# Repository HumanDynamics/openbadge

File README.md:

# OpenBadge project #

Welcome to the Open Badge project, an open-source framework and toolkit for measuring and shaping face-to-face social interactions using either custom hardware devices or smart phones, and real-time web-based visualizations. Open Badges is a modular system that allows researchers to monitor and collect interaction data from people engaged in real-life social settings. For more information, please read our main publications ([1](https://ieeexplore.ieee.org/document/8259434),[2](https://www.media.mit.edu/publications/rhythm-a-unified-measurement-platform-for-human-organizations/),[3](https://www.media.mit.edu/publications/open-badges-a-low-cost-toolkit-for-measuring-team-communication-and-dynamics/)) ,visit our [wiki](https://github.com/HumanDynamics/OpenBadge/wiki), or join our [discussion forum](https://groups.google.com/d/forum/rhythm-badges).

Additional repositories that are part of this project:
* https://github.com/mitmedialab/rhythm-badge-programmer - schematics, vector files and instructions for making a programming rig 

* https://github.com/HumanDynamics/openbadge-hub-py - a python based hub (base station) for pulling data from badges

* https://github.com/HumanDynamics/openbadge-hub - a Javascript/Cordova app that communicates with the badges and stores
 the data to a server
* https://github.com/HumanDynamics/openbadge-server - the backend server for the app

* https://github.com/HumanDynamics/openbadge-analysis - Python (2.7) package for loading and pre-processing badge data

* https://github.com/HumanDynamics/openbadge-analysis-examples - Examples showing how to use the analysis package

## Docker wrapper ##
The nRF working environment is now available as a Docker container. The following commands have been tested under Ubuntu
linux, but should work under iOS as well (with some modifications, especially to the device names).

Important notes:
1. The badge must be connected to the programmer before starting the docker (using docker-compose run)
2. Docker will mount the project directory under /app inside the container, so the container can see the latest changes
 (no need to build the container after every code change)

Commands:
* docker-compose build : builds the docker container "nrf". You must run this command at least once before calling
 docker-compose run.
* docker-compose run nrf <COMMAND> : where <COMMAND> is a command to run inside the container.
  * When calling make (e.g. make badge_03v6_noDebug flashUnlock flashErase  flashS130 flashAPP), the script will automatically
  change the working directory to the data_collector directory. You can see the different make options by calling:
  "docker-compose run nrf make"
* docker-compose run nrf bash : opens an interactive bash shell
* ./programming_loop_docker.sh [test/prod] : a utility used for programming a batch of badges. It will compile once, and
 then enters a loop. Each time a new badge is placed, it will be automatically programmed and its MAC address will be
 written to the macs.log file. For most purposes, use the "prod" command variables. The "test" option turns on serial
 output and other testing features and is not recommended for production.

If you are using a raspberry pi to run this code, please use the raspberry pi compose file (-f docker-compose-raspi.yml). For example `docker-compose -f docker-compose-raspi.yml build`.

## Firmware testing tools ##
The framework includes two tools for testing firmware code
* Badge terminal. The utility opens a connections to a badge and allows you to run simple commands. To run, use the following docker command: `docker-compose run nrf terminal <MAC ADDRESS>`
* Integration tests. These are tests designed for testing basic badge functionality. To run the tests, use the following docker command: `docker-compose run nrf run_all_tests <MAC ADDRESS>`

Note that in order to run the integration tests, you'll need to have a badge connected with a serial interface. A regular J-Link debugger/programmer does not include these. We recommend using a nRF51 dev-kit as a programmer for this purpose (see our wiki/documentations on how to make one).

## Badge testing procedure ##
The badge firmware includes a tester mode that can be used for testing new badges. 
To compile, use the badge_03v6_tester flag (or badge_03v4_tester, for older hardware). For example:
```
make badge_03v6_noDebug flashUnlock flashErase  flashS130 flashAPP
```

Or, when using docker:
```
docker-compose run nrf make badge_03v6_noDebug flashUnlock flashErase  flashS130 flashAPP
```

Once programmed, the badge uses the LEDs to indicate the status of the test:
1. Blink red LED several times, one for each test (EEPROM, Flash, etc)
2. Microphone test. When it starts, both green and red LEDs will turn on 
It then looks for quiet->noise->quiet->noise pattern, each section must be at least 200 ms long. 
This must be completed within 10 seconds.
In a quiet place, simply say "ahhhh" twice, with pause in between. Every time the noise passed the threshold, the LEDs 
will turn off
3. Accelerometer test. When it starts, both green and red LEDs will turn on. Simply shake the badge
4. Once done, the green LED will turn off for several seconds and then turn off

Example for known issues with badge manufacturing:
* LEDs not turning on - might be a problem with the LEDs themselves
* When microphone test starts, both LEDs will momentarily turn on and then off
This might indicate a problem in the microphone filter or amplifier circuit (the microphone saturates and noise level says high)

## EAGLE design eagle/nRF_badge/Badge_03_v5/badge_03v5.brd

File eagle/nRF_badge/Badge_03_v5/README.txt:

Note - we have not manufactured this version yet

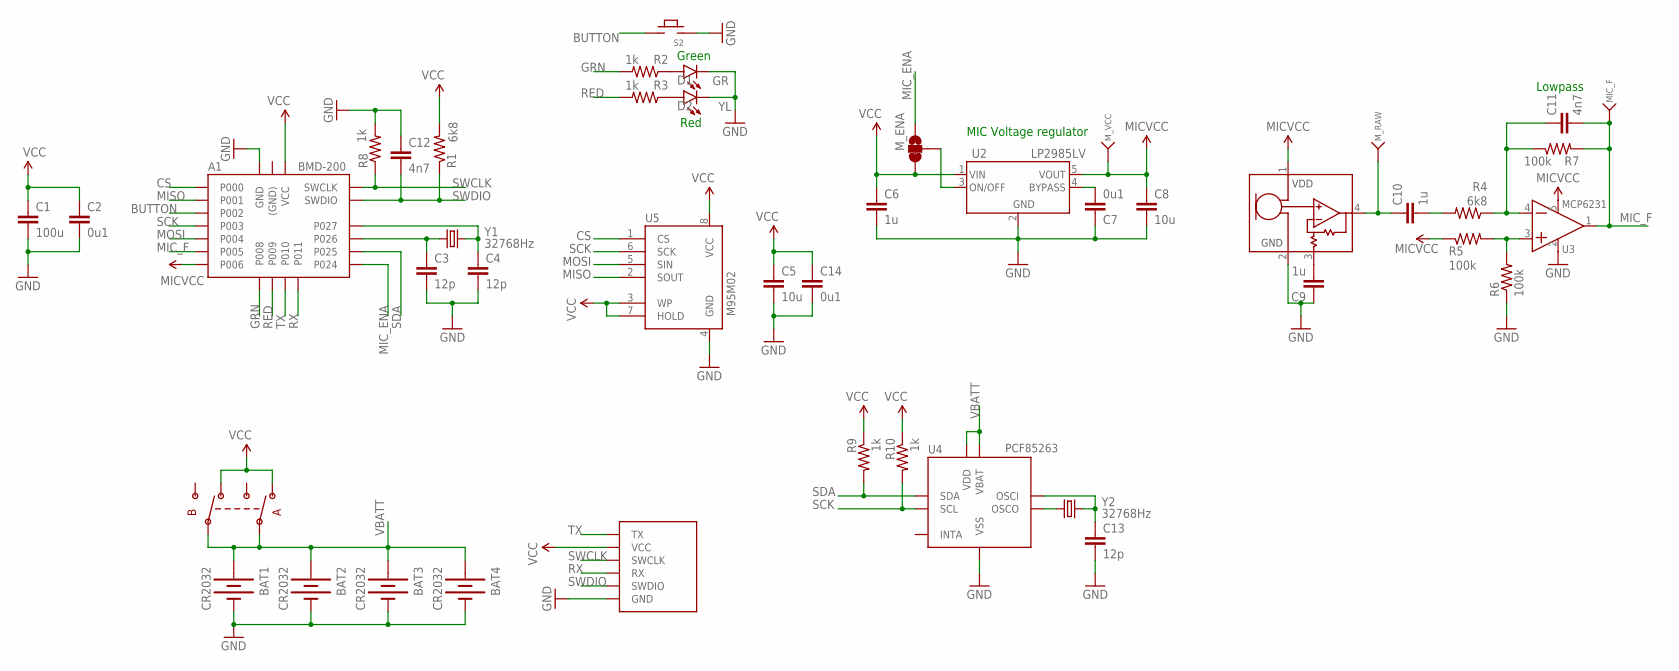
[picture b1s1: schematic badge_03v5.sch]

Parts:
A1: BMD-200
BAT1, BAT2: CR2032; BATTCON_20MM_4LEGS_ISO_NOCREAM
BAT3: CR2032; BU2032SM
BAT4: CR2032; BU2032SM_CREAM
C1: 100u; C1206
C2, C7, C14: 0u1; C0603
C3, C4, C13: 12p; C0603
C5, C8: 10u; C0603
C6, C9, C10: 1u; C0603
C11, C12: 4n7; C0603
D1: GR; LED-0603
D2: YL; LED-0603
J1: PROG_CONN_6; TH_CONN_6
MIC_F: TESTPOINT
MK1: SPU0414; MIC_SPU041X
M_ENA: JUMPER-PAD-3-2OF3_NC_BY_TRACE_SMALL; PAD-JUMPER-3-2OF3_NC_BY_TRACE_YES_SILK_FULL_BOX
M_RAW: TESTPOINT
M_VCC: TESTPOINT
R1, R4: 6k8; R0603
R2, R3, R8, R9, R10: 1k; R0603
R5, R6, R7: 100k; R0603
S1: DPDT; JS202011SCQN
S2: TACT6mm; TACT1
U2: LP2985LV; SOT23-5L
U3: MCP6231; SOT23-5L
U4: PCF85263; SOIC8
U5: M95M02; SOIC8
Y1, Y2: 32768Hz; CRYSTAL_2SMD

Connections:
BUTTON: A1.P$13 (P002), S2.1, S2.2
CS: A1.P$11 (P000), U5.1 (CS)
GND: A1.P$1 (GND), A1.P$2 (GND), A1.P$3 (GND), A1.P$4 (GND), A1.P$7 (GND), A1.P$10 (GND), A1.P$19 (GND), A1.P$26 (GND), BAT1.NEG (-), BAT2.NEG (-), BAT3.-, BAT4.-, C1.2, C2.2, C3.2, C4.2, C5.2, C6.2, C7.1, C8.2, C9.1, C12.1, C13.2, C14.2, D1.C, D2.C, J1.GND, MK1.2 (GND), R6.1, R8.2, S2.3, S2.4, U2.2 (GND), U3.2 (GND), U4.4 (VSS), U5.4 (GND)
GRN: A1.P$20 (P008), R2.2
MICVCC: A1.P$17 (P006), C8.1, MK1.1 (VDD), M_VCC.P$1, R5.1, U2.5 (VOUT), U3.5 (VDD)
MIC_ENA: A1.P$5 (P024), M_ENA.1
MIC_F: A1.P$16 (P005), C11.2, MIC_F.P$1, R7.2, U3.1 (O)
MISO: A1.P$12 (P001), U5.2 (SOUT)
MOSI: A1.P$15 (P004), U5.5 (SIN)
unnamed: U4.2 (OSCO), Y2.P$2 (2)
unnamed: A1.P$8 (P026), C3.1, Y1.P$2 (2)
unnamed: D1.A, R2.1
unnamed: D2.A, R3.1
unnamed: C13.1, U4.1 (OSCI), Y2.P$1 (1)
unnamed: M_ENA.2, U2.3 (ON/OFF)
unnamed: C9.2, MK1.3 (GAIN)
unnamed: A1.P$9 (P027), C4.1, Y1.P$1 (1)
unnamed: C7.2, U2.4 (BYPASS)
unnamed: R5.2, R6.2, U3.3 (+)
unnamed: C10.1, MK1.4 (OUT), M_RAW.P$1
unnamed: C10.2, R4.2
unnamed: C11.1, R4.1, R7.1, U3.4 (-)
RED: A1.P$21 (P009), R3.2
RX: A1.P$23 (P011), J1.RX
SCK: A1.P$14 (P003), R10.2, U4.6 (SCL), U5.6 (SCK)
SDA: A1.P$6 (P025), R9.2, U4.5 (SDA)
SWCLK: A1.P$25 (SWCLK), J1.SWCLK, R8.1
SWDIO: A1.P$24 (SWDIO), C12.2, J1.SWDIO, R1.1
TX: A1.P$22 (P010), J1.TX
VBATT: BAT1.1 (+), BAT1.2 (+), BAT1.3 (+), BAT1.4 (+), BAT2.1 (+), BAT2.2 (+), BAT2.3 (+), BAT2.4 (+), BAT3.+, BAT4.+, S1.AC, S1.BC, U4.3 (VBAT), U4.8 (VDD); also elsewhere on the board
VCC: A1.P$18 (VCC), C1.1, C2.1, C5.1, C6.1, C14.1, J1.VCC, M_ENA.3, R1.2, R9.1, R10.1, S1.A1, S1.B1, U2.1 (VIN), U5.3 (WP), U5.7 (HOLD), U5.8 (VCC); also elsewhere on the board

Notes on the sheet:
Green
Red
MIC Voltage regulator
Lowpass

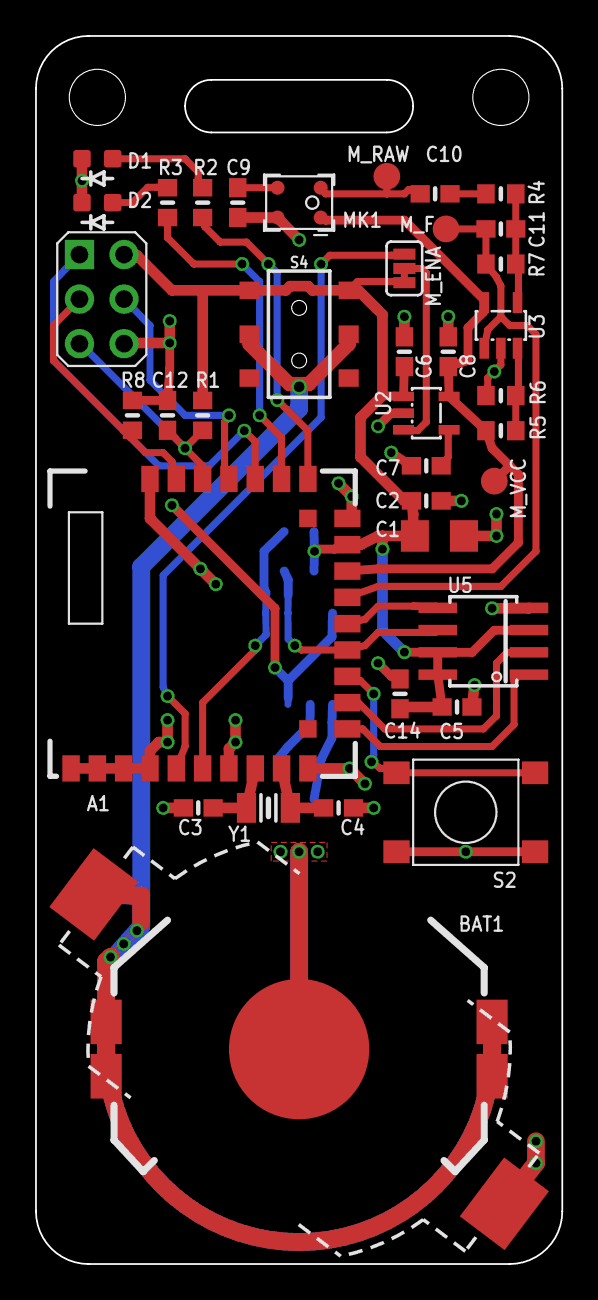
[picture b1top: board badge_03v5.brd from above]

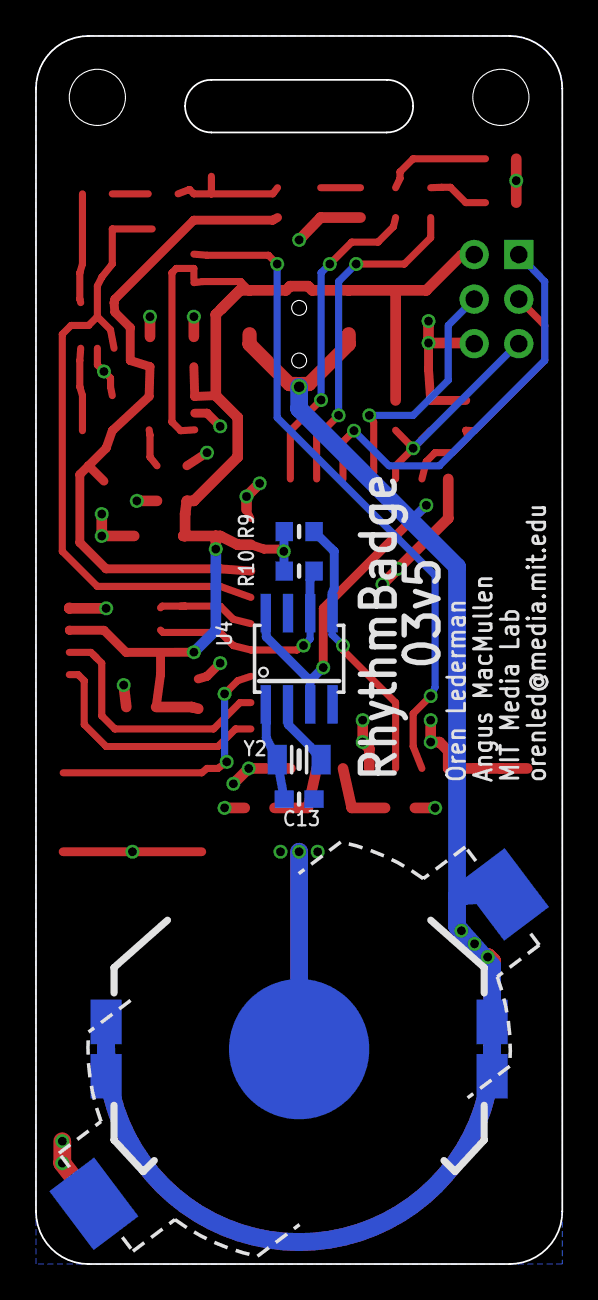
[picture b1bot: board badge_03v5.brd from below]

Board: 2 copper layers, 30.0 x 70.0 mm, 45 parts (7 on the bottom side), 31 nets.

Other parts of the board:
S4: DPDT; SWITCH_DPDT_SMD_AYZ0202

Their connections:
VBATT: S4.2, S4.5; also elsewhere on the board
VCC: S4.1, S4.4; also elsewhere on the board

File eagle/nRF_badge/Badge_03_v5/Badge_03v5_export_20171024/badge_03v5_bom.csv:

Part,Value,Digikey#
A1,BMD-200,1604-1004-1-ND
BAT4,CR2032,BU2032SM-BT-GCT-ND
C1,100u,490-4539-1-ND
C2,0u1,490-1532-1-ND
C3,12p,490-1405-1-ND
C4,12p,490-1405-1-ND
C5,10u,490-6405-1-ND
C6,1u,490-1543-1-ND
C7,0u1,490-1532-1-ND
C8,10u,490-6405-1-ND
C9,1u,490-1543-1-ND
C10,1u,490-1543-1-ND
C11,4n7,1276-1098-1-ND
C12,4n7,1276-1098-1-ND
C13,12p,490-1405-1-ND
C14,0u1,490-1532-1-ND
D1,GR,475-2709-1-ND
D2,YL,475-2712-1-ND
MK1,SPU0414,423-1134-1-ND
R1,6k8,RMCF0603JT6K80CT-ND
R2,1k,311-1.0KGRCT-ND
R3,1k,311-1.0KGRCT-ND
R4,6k8,RMCF0603JT6K80CT-ND
R5,100k,311-100KGRCT-ND
R6,100k,311-100KGRCT-ND
R7,100k,311-100KGRCT-ND
R8,1k,311-1.0KGRCT-ND
R9,1k,311-1.0KGRCT-ND
R10,1k,311-1.0KGRCT-ND
S4,DPDT,401-2013-1-ND
S2,TACT6mm,CKN9087CT-ND
U5,M95M02,497-11405-1-ND
U2,LP2985LV,296-18474-1-ND
U3,MCP6231,MCP6231T-E/OTCT-ND
U4,PCF85263,568-12405-1-ND
Y1,32768Hz,535-11937-1-ND
Y2,32768Hz,535-11937-1-ND

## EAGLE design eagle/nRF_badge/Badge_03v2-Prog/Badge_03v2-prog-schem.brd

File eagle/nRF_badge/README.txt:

Eagle files for nRF51 based badges and programmers

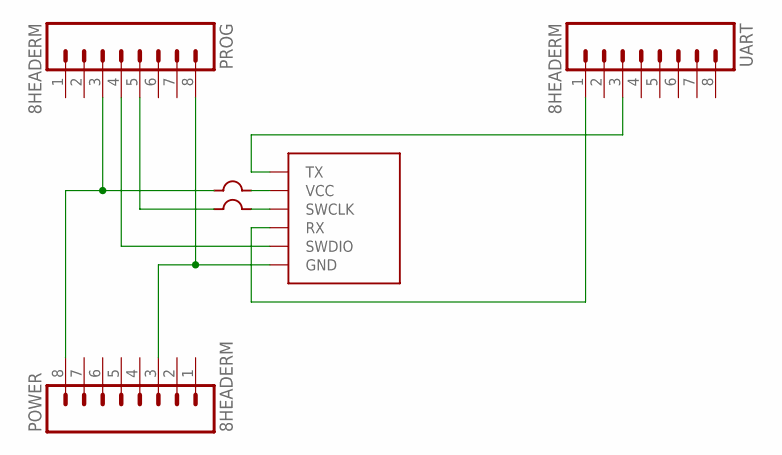
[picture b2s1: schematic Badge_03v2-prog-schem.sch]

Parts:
J1: PROG_CONN_6; TH_CONN_6
POWER: 8HEADERM; 1X08_ROUND
PROG: 8HEADERM; 1X08_ROUND
U$1, U$2: JUMPER; 1206
UART: 8HEADERM; 1X08_ROUND

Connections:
GND: J1.GND, POWER.3, PROG.8
unnamed: J1.VCC, U$1.2
unnamed: J1.SWCLK, U$2.2
unnamed: J1.SWDIO, PROG.4
RX: J1.RX, UART.1
SWCLK: PROG.5, U$2.1
TX: J1.TX, UART.3
VCC: POWER.8, PROG.3, U$1.1

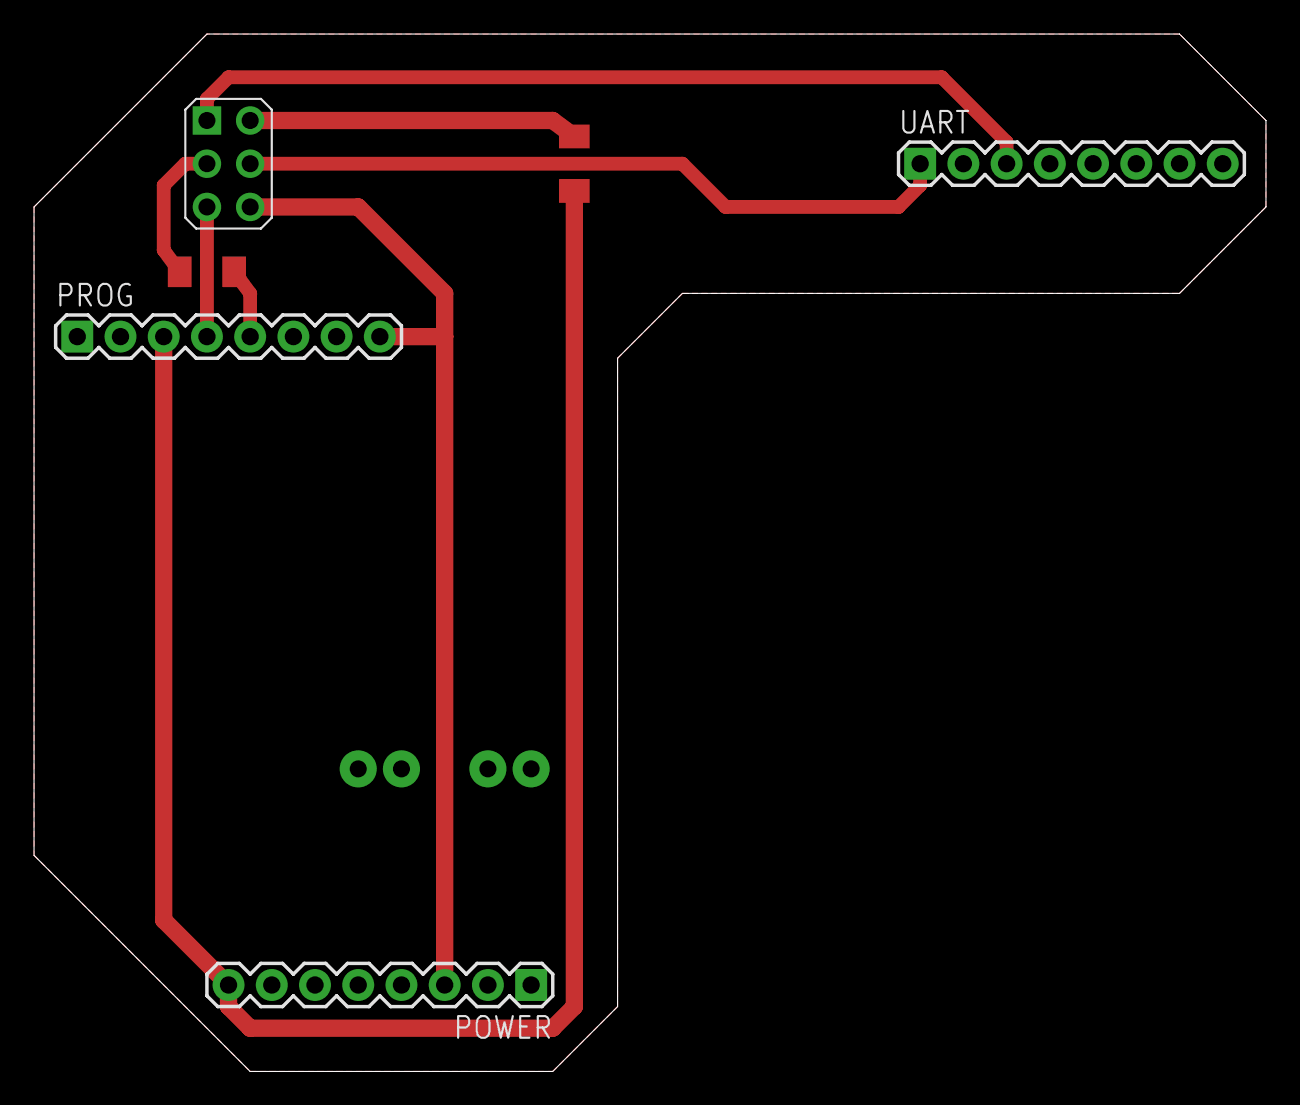
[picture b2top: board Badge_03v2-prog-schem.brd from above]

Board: 2 copper layers, 72.4 x 61.0 mm, 6 parts (0 on the bottom side), 8 nets.

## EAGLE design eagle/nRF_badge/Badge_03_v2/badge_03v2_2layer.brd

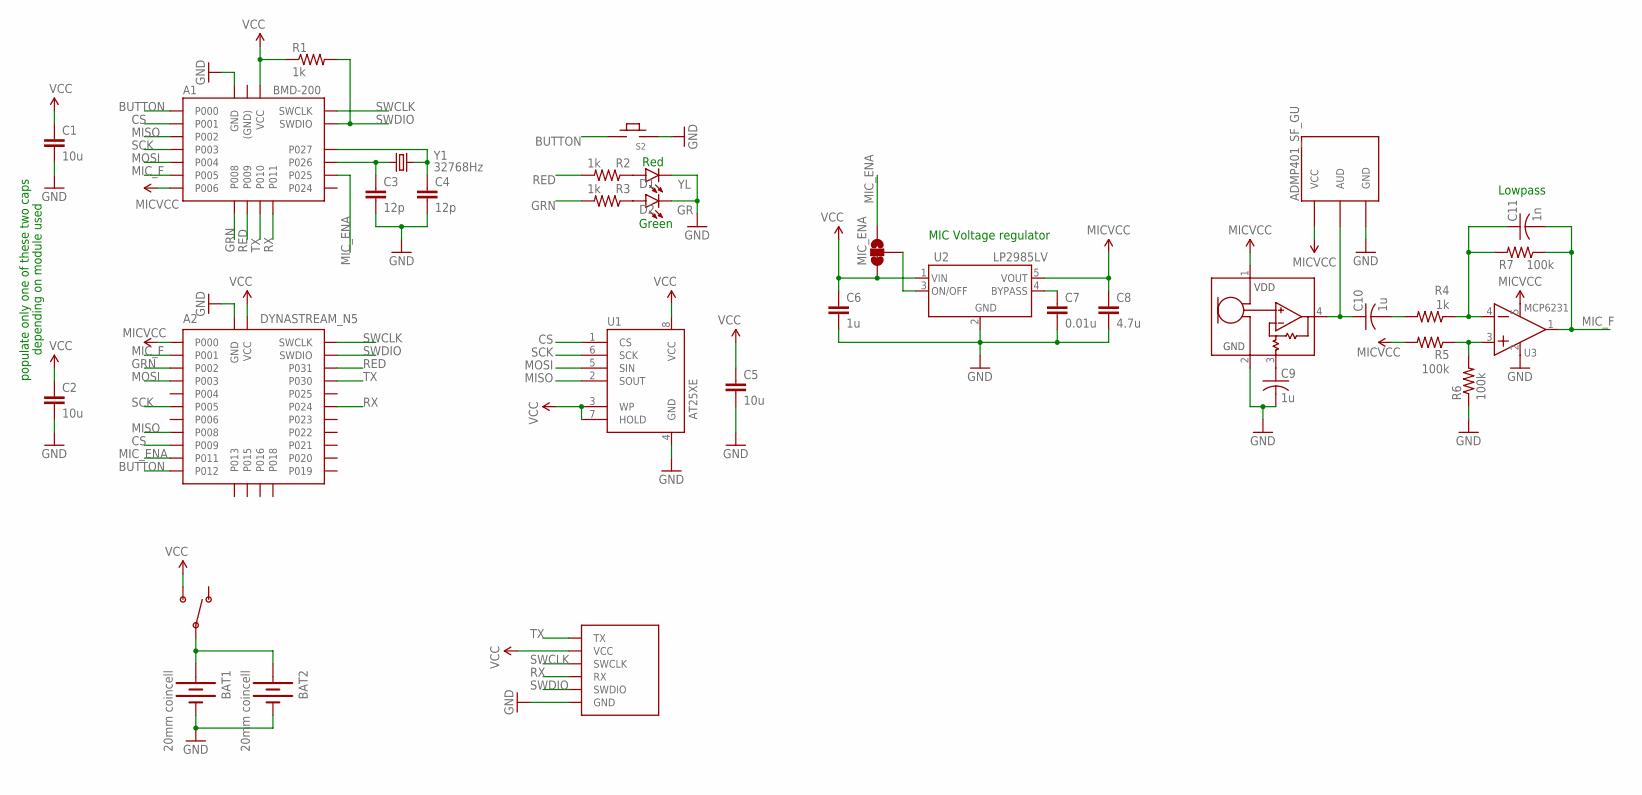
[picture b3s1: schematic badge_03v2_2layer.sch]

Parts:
A1: BMD-200
A2: DYNASTREAM_N5
A3: ADMP401_SF_GU; ADMP401_SF_SMD
BAT1: 20mm coincell; BATTCON_20MM_4LEGS_ISO
BAT2: 20mm coincell; BATTCON_20MM_4LEGS_ISO_NOCREAM
C1, C2, C5: 10u; C0603
C3, C4: 12p; C0603
C6, C9, C10: 1u; C0603
C7: 0.01u; C0603
C8: 4.7u; C0603
C11: 1n; C0603
D1: YL; LED-0603
D2: GR; LED-0603
J1: PROG_CONN_6; TH_CONN_6
MIC_ENA: DC/DC; PAD-JUMPER-3-2OF3_NC_BY_TRACE_YES_SILK_FULL_BOX
MK1: SPU0414(AMP); MIC_SPU041X
R1, R4: 1k; R0603
R2, R3: 1k; 0603-RES
R5, R6, R7: 100k; R0603
S1: CL-SB-12A-01
S2: TACT6MM4; TACT1
U1: AT25XE; SOIC8
U2: LP2985LV; SOT23-5L
U3: MCP6231; SOT23-5L
Y1: 32768Hz; CRYSTAL_2SMD

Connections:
BUTTON: A1.P$11 (P000), A2.D1 (P012), S2.1, S2.2
CS: A1.P$12 (P001), A2.E1 (P009), U1.1 (CS)
GND: A1.P$1 (GND), A1.P$2 (GND), A1.P$3 (GND), A1.P$4 (GND), A1.P$7 (GND), A1.P$10 (GND), A1.P$19 (GND), A1.P$26 (GND), A2.A2 (GND), A2.A3 (GND), A2.A4 (GND), A2.A5 (GND), A2.A6 (GND), A3.GND, A3.GNDT (GND), BAT1.NEG (-), BAT2.NEG (-), C1.2, C2.2, C3.2, C4.2, C5.2, C6.2, C7.2, C8.2, C9.2, D1.C, D2.C, J1.GND, MK1.2 (GND), R6.1, S2.3, S2.4, U1.4 (GND), U2.2 (GND), U3.2 (GND)
GRN: A1.P$20 (P008), A2.F5 (P002), R3.2
MICVCC: A1.P$17 (P006), A2.E5 (P000), A3.VCC, A3.VCCT (VCC), C8.1, MK1.1 (VDD), R5.2, U2.5 (VOUT), U3.5 (VDD)
MIC_ENA: A1.P$6 (P025), A2.E2 (P011), MIC_ENA.1
MIC_F: A1.P$16 (P005), A2.F4 (P001), C11.2, R7.1, U3.1 (O)
MISO: A1.P$13 (P002), A2.F1 (P008), U1.2 (SOUT)
MOSI: A1.P$15 (P004), A2.F3 (P003), U1.5 (SIN)
unnamed: A1.P$8 (P026), C3.1, Y1.P$2 (2)
unnamed: D1.A, R2.1
unnamed: D2.A, R3.1
unnamed: MIC_ENA.2, U2.3 (ON/OFF)
unnamed: C9.1, MK1.3 (GAIN)
unnamed: A1.P$9 (P027), C4.1, Y1.P$1 (1)
unnamed: C7.1, U2.4 (BYPASS)
unnamed: R5.1, R6.2, U3.3 (+)
unnamed: A3.AUD, A3.AUDT (AUD), C10.1, MK1.4 (OUT)
unnamed: C10.2, R4.2
unnamed: C11.1, R4.1, R7.2, U3.4 (-)
RED: A1.P$21 (P009), A2.F6 (P031), R2.2
RX: A1.P$23 (P011), A2.D6 (P024), J1.RX
SCK: A1.P$14 (P003), A2.F2 (P005), U1.6 (SCK)
SWCLK: A1.P$25 (SWCLK), A2.C1 (SWCLK), J1.SWCLK
SWDIO: A1.P$24 (SWDIO), A2.B1 (SWDIO), J1.SWDIO, R1.2
TX: A1.P$22 (P010), A2.E6 (P030), J1.TX
VBATT: BAT1.1 (+), BAT1.2 (+), BAT1.3 (+), BAT1.4 (+), BAT2.1 (+), BAT2.2 (+), BAT2.3 (+), BAT2.4 (+), S1.C
VCC: A1.P$18 (VCC), A2.B5 (VCC), A2.B6 (VCC), A2.C5 (VCC), A2.C6 (VCC), C1.1, C2.1, C5.1, C6.1, J1.VCC, MIC_ENA.3, R1.1, S1.2, U1.3 (WP), U1.7 (HOLD), U1.8 (VCC), U2.1 (VIN)

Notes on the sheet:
Green
Red
MIC Voltage regulator
Lowpass
populate only one of these two caps
depending on module used

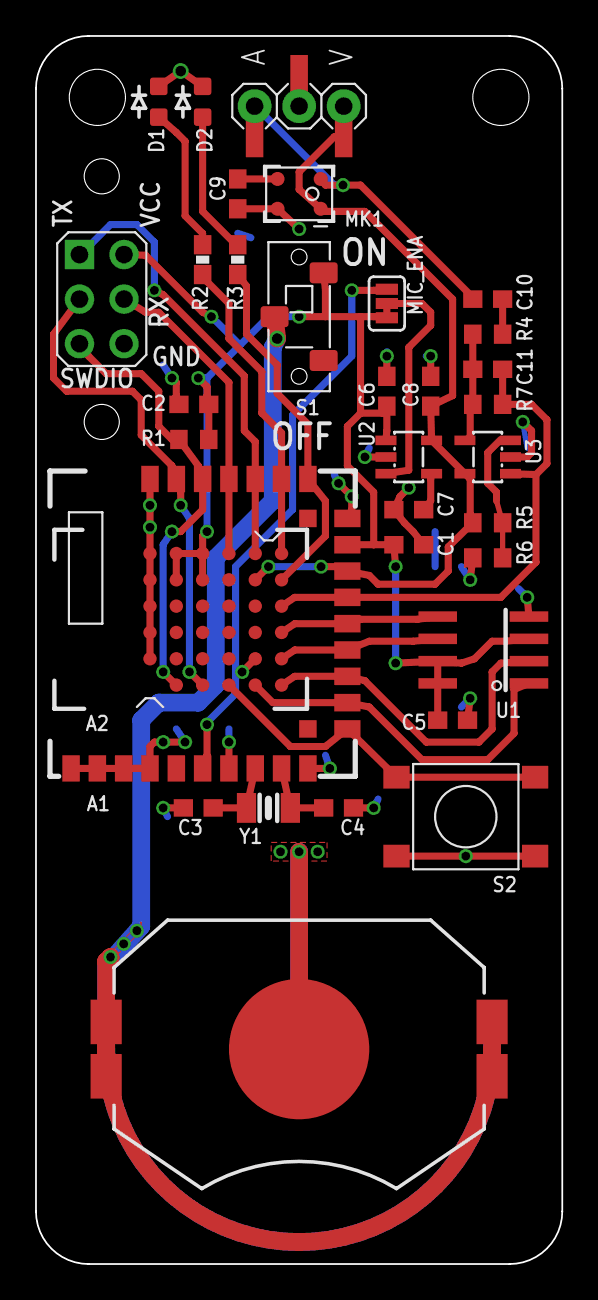
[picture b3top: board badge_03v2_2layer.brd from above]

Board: 2 copper layers, 30.0 x 70.0 mm, 34 parts (1 on the bottom side), 28 nets.

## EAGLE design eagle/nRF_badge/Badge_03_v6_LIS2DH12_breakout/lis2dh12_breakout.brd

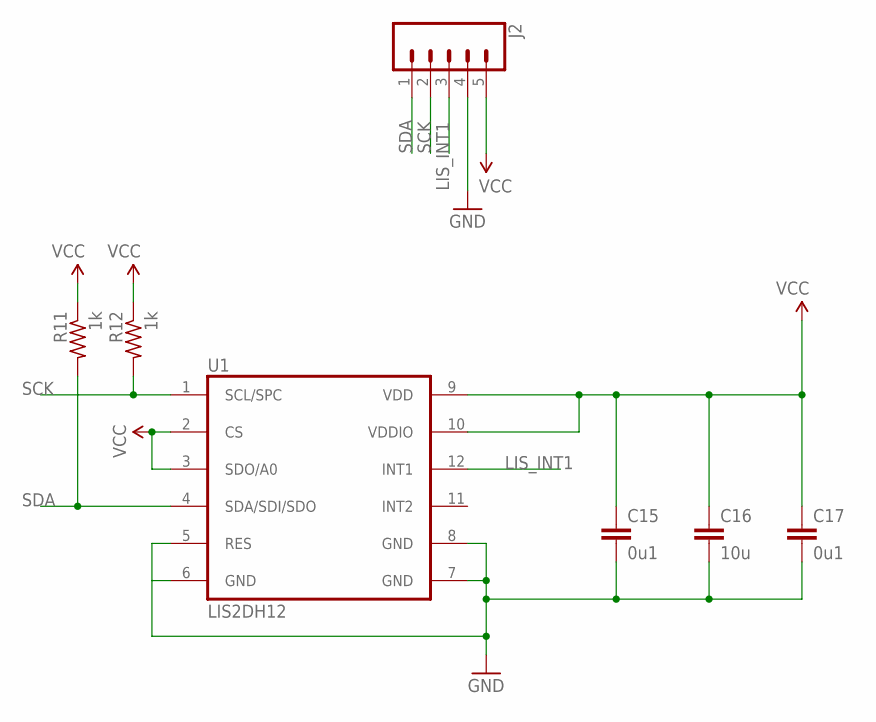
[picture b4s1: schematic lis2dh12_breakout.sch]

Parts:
C15, C17: 0u1; C0603
C16: 10u; C0603
J2: CONN_05NO_SILK; 1X05_NO_SILK
R11, R12: 1k; R0603
U1: LIS2DH12; LGA12

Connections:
GND: C15.2, C16.2, C17.2, J2.4, U1.5 (RES), U1.6 (GND), U1.7 (GND), U1.8 (GND)
LIS_INT1: J2.3, U1.12 (INT1)
SCK: J2.2, R12.2, U1.1 (SCL/SPC)
SDA: J2.1, R11.2, U1.4 (SDA/SDI/SDO)
VCC: C15.1, C16.1, C17.1, J2.5, R11.1, R12.1, U1.2 (CS), U1.3 (SDO/A0), U1.9 (VDD), U1.10 (VDDIO)

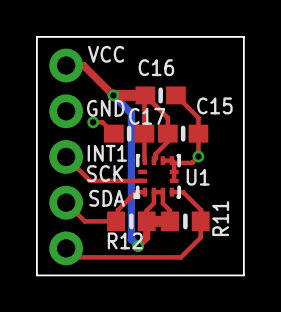
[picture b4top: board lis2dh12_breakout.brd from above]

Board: 2 copper layers, 11.5 x 13.2 mm, 7 parts (0 on the bottom side), 5 nets.

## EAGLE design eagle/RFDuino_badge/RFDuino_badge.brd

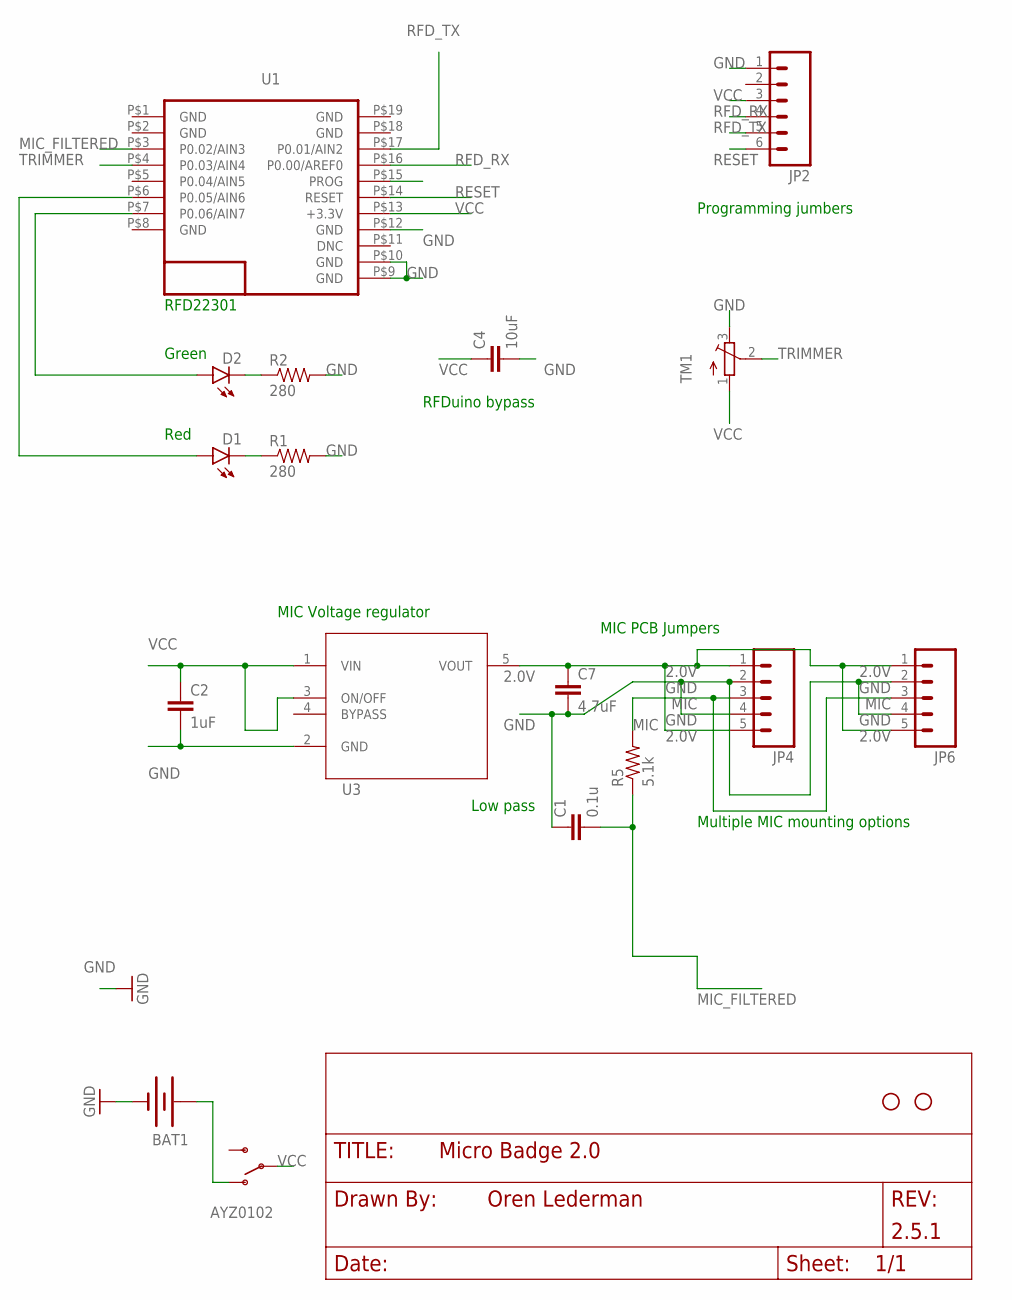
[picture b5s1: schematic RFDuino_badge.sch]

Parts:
AYZ0102: AYZ0102AGRLCAYZ0102AGRLC; KPS-1290
BAT1: BATTERY20MM_4LEGS_OVERPASTE; BATTCON_20MM_4LEGS_OVERPASTE
C1: 0.1u; 1206
C2: 1uF; 1206
C4: 10uF; 1206
C7: 4.7uF; 1206
D1, D2: LED1206; LED-1206
JP2: M06LONGPADS; 1X06_LONGPADS
JP4: M05PTH_LONGPADS; 1X05_LONGPADS
JP6: M05PTH; 1X05
R1, R2: 280; 1206
R5: 5.1k; 1206
STANDOFF1, STANDOFF2: STAND-OFF
TM1: TRIMPOTTC33X; TC33X
U1: RFD22301; RFD21733
U3: LP2985AIM5-2.5; SOT95P285X120-5N

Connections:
2.0V: C7.1, JP4.1, JP4.5, JP6.1, JP6.5, U3.5 (VOUT)
AIN6: D1.A, U1.P$6 (P0.05/AIN6)
AIN7: D2.A, U1.P$7 (P0.06/AIN7)
GND: BAT1.2 (-), C1.1, C2.2, C4.2, C7.2, JP2.1, JP4.2, JP4.4, JP6.2, JP6.4, R1.2, R2.2, TM1.3 (E), U1.P$9 (GND), U1.P$10 (GND), U1.P$12 (GND), U3.2 (GND)
MIC: JP4.3, JP6.3, R5.2
MIC_FILTERED: C1.2, R5.1, U1.P$3 (P0.02/AIN3)
unnamed: AYZ0102.O, BAT1.1 (+)
unnamed: D2.C, R2.1
unnamed: D1.C, R1.1
RESET: JP2.6, U1.P$14 (RESET)
RFD_RX: JP2.4, U1.P$16 (P0.00/AREF0)
RFD_TX: JP2.5, U1.P$17 (P0.01/AIN2)
TRIMMER: TM1.2 (S), U1.P$4 (P0.03/AIN4)
VCC: AYZ0102.P, C2.1, C4.1, JP2.3, TM1.1 (A), U1.P$13 (+3.3V), U3.1 (VIN), U3.3 (ON/OFF)

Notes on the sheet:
RFD22301
Green
Red
RFDuino bypass
MIC PCB Jumpers
MIC Voltage regulator
Programming jumbers
Low pass
Multiple MIC mounting options

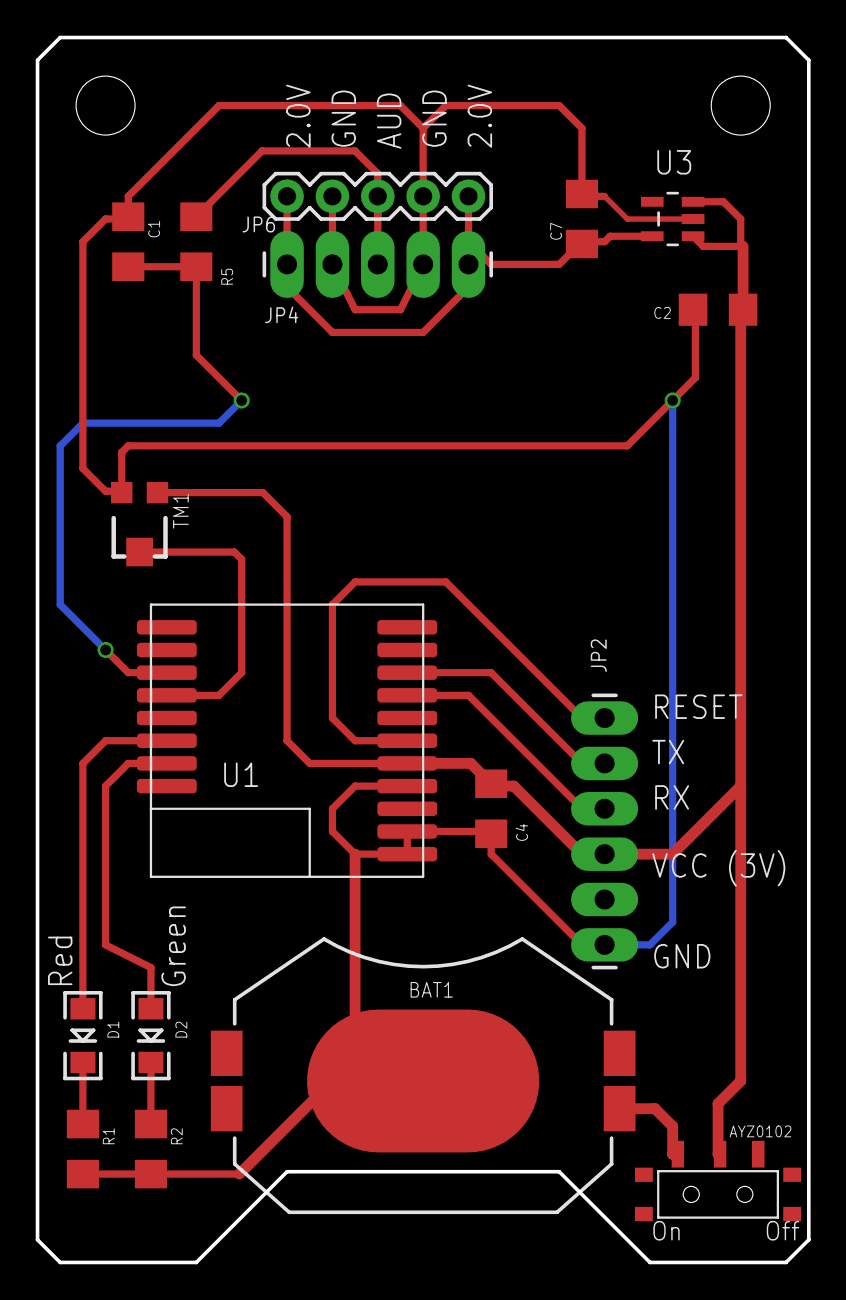
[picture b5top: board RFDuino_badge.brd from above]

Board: 2 copper layers, 43.2 x 68.6 mm, 19 parts (0 on the bottom side), 14 nets.

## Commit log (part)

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2016-10-31 Include app_timer in build
2016-10-31 Disable BLE timeout and improve integration test.
2016-10-31 Update debug log test
2016-11-03 Add automatic test case runner
2016-11-03 Integration test runner works nicely
2016-11-03 Improved millis() implementation
2016-11-03 Code cleanup, has reset command and works
2016-11-03 progress
2016-11-03 Fix bug in badge.py that was causing test failures
2016-11-14 Revert change
2016-12-02 Some changes
2016-12-11 Kill noisy debug log
2016-12-11 Remove debug log line
2016-12-12 Clean up storer so it's less miserable to work with.
2016-12-12 First attempt at new methodology
2016-12-12 Sample more often but take fewer readings
2016-12-12 Remove sleep instrumentation
2016-12-15 Improved battery sampling.
2016-12-15 Add firmware version to Makefile automatically
2016-12-19 Add new command to terminal with different audio data representation
2016-12-21 Restore BLE Timeouts
2016-12-21 Have badge.py in BadgeFramework default to same scan settings as hub-py
2016-12-21 New Startup LED animation
2017-01-10 Make clock increment an atomic operation.
2017-01-10 Make sure test failures are propogated.
2017-01-11 Mostly working google tests
2017-01-11 Setup test file for flash_layout_utils
2017-01-11 Run tests automatically on compile
2017-01-11 Clean up unit test make file a little.
2017-01-11 Wrote some unit tests for flash.c
2017-02-08 Flash API Work
2017-06-14 Playbook is no longer relevant
2017-06-21 Adding a script for programming badges in a loop
2017-07-23 Saving raspi docker config in a separate set of files. Updating ubuntu docker to use JLink 6
2017-10-24 Created new eagle version. Added BAT variant with no cream in center. Replaced top part to new variant
2017-10-24 Replaced AT25M02 with M95M02
2017-10-24 Minor changes. Generated centroids and bom
2017-11-02 Commenting out the internal flash test until we fix the issue
2017-11-03 Changed writing on the back to Rhythm badge
2017-11-07 Cleanning up labels
2017-11-08 Simple breakout board design for LIS2DH12
2017-11-19 Changed power traces in 3v05
2017-11-19 Traces cleanup
2017-12-01 Added sleep after new badge is identified in the programming loop (otherwise it fails)
2017-12-03 Removing button test
2018-01-12 change component for comliant design with technical note TN0018
2018-01-12 New modified component for LIS2DH added to master library
2018-01-17 Approved Overlap in jumpar pad, errors is cause by DRC but package is fine.
2018-01-19 Add LIS3DH implemented.
    1- Added a new board badge_03v6 , and new makefile flags (badge_03v6, badge_03v6_noDebug, badge_03v6_tester).
    2- Removed the references to the button in the code and tester code.
    3-Used and improve "whoami" (implemented by Oren) for make sure that accelerometer is connected.
    4- LIS3DH internal self-test. (Simulated aceleration when device is static (by register) and enable interruput pin that is read by interrupt pin input in your nrf51)
    5- Activated a internal motion detection for wake up the badge. (When movement is detected LIS3DH enable Interruput output that is read by your nrf51)
    6- Implemented too a tap feature for detect movement.
2018-01-24 Accel firmware. Remove button. Makefile flags.
    1- Added a new board badge_03v6 , and new makefile flags (badge_03v6, badge_03v6_noDebug, badge_03v6_tester).
    2- Removed the references to the button in the code and tester code.
    3-Used and improve "whoami" (implemented by Oren) for make sure that accelerometer is connected.
    4- LIS3DH internal self-test. (Simulated aceleration when device is static (by register) and enable interruput pin that is read by interrupt pin input in your nrf51)
    5-Activated a internal motion detection for wake up the badge. (When movement is detected LIS3DH enable Interruput output that is read by your nrf51)
    6-Implemented too a tap feature for detect movement.
2018-01-27 Corrected dot position
2018-01-31 Updated DRC. Fix location of pin#1 dot in LIS2DH12 package
2018-01-31 Reverting DRC changes
2018-02-01 Changes LIS2DH12 footprints to fit the devkit's traces
2018-02-16 Testing fork
2018-02-16 Serial RSSI ranging code
2018-02-16 static vs antistatic ranging test data
2018-02-21 Can convert logs to csv now and started jupyter notebook with pandas to analyze data
2018-02-21 Loaded in CSVs and started graphing the data. Need to come up with a clean way to analyze all of the combinations (Anti v NoAnti on both Transmitters and Receiver)
2018-02-22 Several plot improvements, including a function that makes it really easy to plot all the data at once. Looks like choosing the max of the rolling mean is the bext option so far
2018-03-01 Cleanup
    Reverse the orginal NRF_SDK_PATH
    Create accel.c and accel.h for the whole accel code.
    CTRL_REG1 define value.
    Change documentation of LIS3DH to LIS2DH.
    Change the name value "prueba" to "tx".
    move the call to accel_spi_init() out of accel_test().
2018-03-02 Update docker for badge_03v6
    Update docker files for badge_03v6
    Add accel.c and accel.h in CMakeLists.txt
2018-03-02 made rssi_scanner directory, data_collector now original version
2018-03-08 Cleaned up holder_analysis, ran new tests to compare effect of different batches on RSSI/rangin accuracy
2018-03-08 cleaning up remote repo
2018-03-22 Test of badge rssi strength ranging by batch, holder type, and distance + some analysis
2018-03-23 Analyzing rssi ranging by batch, holdertype, and distance
2018-03-29 Some cleanup
2018-03-29 Removing data files
2018-03-29 RSSI scanner
    A variation of the firmware that scans for other badges and outputs the MACs and RSSIs to serial
2018-04-13 test commit
2018-04-27 Testing method for prioritizing beacons
2018-05-08 UART and LED test
2018-05-08 Starting developing a testing environment with one example test file
2018-05-08 beacon tests finalized
2018-05-10 Added error code returns to ADC and SPI and Accel read out test
2018-05-11 New LED startup sequence
2018-05-12 Started implementing uart lib, and added instance array bug in spi lib
2018-05-14 SPI renaming fixes
2018-05-15 Implemented UART Driver
2018-05-15 Added NULL check before dereferencing instance-arrays
2018-05-16 Startet testing LCOV and GCOV
2018-05-29 Started Flash implementation
2018-05-30 Removed automatic store check capability in store success callback
2018-06-01 Added blocking function for store and erase to flash-lib
2018-06-01 Implemented an system event-lib to register for system events
2018-06-04 Edit the comments
2018-06-05 Changed uart module that different instances on the same peripheral is allowed
2018-06-05 Fixed bug in spi-handler
2018-06-05 Changed capability to have more than one instance on same peripheral
2018-06-06 Added RAM check for data
2018-06-06 Small comment changes
2018-06-07 Started adding FreeRTOS to docker
2018-06-08 Implemented Mock modules for flash and EEPROM and a Makefile
2018-06-09 Started set up of googletest framework
2018-06-12 Added capability to remove zero called files from LCOV-report
2018-06-14 Unit tests for eeprom- and flash-mock
2018-06-17 Changes in eeprom & flash mocks and unittests
2018-06-19 Finished storage1 implementation
2018-06-20 Added multiple initialization capability to storage1 and storage2
2018-06-22 Added NRF_ERROR_TIMEOUT to storage2_init doc
2018-06-24 Added storage display capability in textfile
2018-06-28 When there is a write to STORAGE1_SIZE - 1, no address will be inserted
2018-07-06 Storage_1 lib changed to no insert at end of unit
2018-07-18 Cleaned up
2018-07-21 Timer implementation based on pthread
2018-07-22 App-timer mock module implementation
2018-07-22 App scheduler mock implementation
2018-07-24 Changed timer-init function
2018-08-07 Badge 3v06 (#100)
    A new hardware version of the badge. Main changes:
    Accelerometer
    * Removed real-time clock and all components from the back of the badge
    * Removed button
    * New on/off switch (more pick&place friendly)
    * New battery holder
2018-08-08 Update Dockerfile to use latest Ubuntu
2018-08-08 Updating docker files to install bluetooth requirements
2018-08-10 Added a comment to store-function
2018-08-10 Giving docker access to com ports
2018-08-10 Cleanning up the ble_badge_connection code
2018-08-13 Fixing timestamp handling bug
2018-08-13 Adding an entry points and short docs for the terminal and integration tests
2018-08-13 Small updates to the docker files
2018-08-13 Migrating BadgeFramework and IntegrationTests to use bluepy (#102)
    * Migrated code to use bluepy instead of Adafruit's blueooth module
    * Added Docker wrapper
    * Added basic commands to README
    Thank you @abhimnc for your contribution!
2018-08-14 Fixing definition for count in ScanDataDevice (should by signed char)
2018-08-14 Fixing raspi issues
2018-08-20 Callback- and data-generator implementation and accelerometer-abstraction (mock)
2018-08-22 Added EXPECT_ARRAY_EQ to gtest.h for easier array comparisions
2018-08-22 Chunk FIFO implementation
2018-08-24 Fixed bugs in chunk_fifo_lib
2018-08-25 Added max_num_samples to accel_read_acceleration()
2018-08-27 Changed app_timer_cnt_get() to microseconds resolution
2018-08-30 Added timeout functionallity to blocking functions
2018-08-31 Added debug_log_bkgnd()-function for non-blocking prints
2018-09-04 Started implementing/integrating protobuf/nanopb
2018-09-14 Changed ble transmit return
2018-09-15 Changed decode-function in tinybuf as classmethod in python
2018-09-16 Changed unit-test Makefile
2018-09-20 Added support for empty messages
2018-09-20 Added tests for empty message in tinybuf
2018-09-21 Added selectable big/little endian format for encoding/decoding
2018-09-21 Small changes to existing modules
2018-09-22 Added clear functionality to filesystem and storage modules
2018-09-23 Edited store/read function to only blocking and fixed large data store/read issue
2018-09-23 Changed number of bytes per clear operation to 128
2018-09-23 Fixed queue bug in BLE badge connection
2018-09-23 Implemented microphone and battery abstraction
2018-09-24 Implemented circular-fifo
2018-09-25 Some small changes
2018-09-29 Added average for battery measurement
2018-09-30 Changed status flags and read badge-assignement in init()
2018-09-30 Added oneof-tags to python file
2018-09-30 Added __repr__ to tinybuf generator in classes
2018-10-01 Implemented timeout_lib
2018-10-02 Added timeout to sender_lib
2018-10-03 First running version (some comments missing)
2018-10-04 Changed timeout request to minutes
2018-10-06 Added clear partition functionality
2018-10-06 Changed battery processing to only store when clock synced
2018-10-06 Storing badge-assignement only if necessary
2018-10-06 Only restart sampling if not already running
2018-10-06 Added LED inidcation to selftest
2018-10-08 Added iterator conflict check when storing (and manual iterator invalidation)
2018-10-11 Changed LED signaling
2018-10-11 Added app_scheduler.h to mock-directory because of word-alignment issue of APP_SCHED_EVENT_HEADER_SIZE
2018-10-13 Changed battery sampling procedure
2018-10-15 Optimized current consumption
2018-10-18 Changed debugging to work with FIFO and added Module description to each print-out
2018-10-18 Changed microphone sampling
2018-10-19 test to check repeated rec/scan request handling
2018-10-21 Added ID and group reset (0xFFFF, 0xFF)
2018-10-21 Implemented microphone selftest with pattern search
2018-10-21 Updated scan integration unittest
2018-10-26 Fixed issue that scanner doesn't time out when a parameter is false
2018-10-26 Add test to scan-unittest to check false scanner input parameters
2018-10-28 Implement moving average clock synchronization
2018-10-31 Support restart command in debug mode and small integration test adjustments
2018-11-01 Change timeout behaviour of sender https://github.com/MichaelHopfengaertner/openbadge/issues/2
2018-11-09 Added reset command to the new protocol
2018-11-09 Update test 4 to use new protocol
    also fixed missed update in test 2
2018-11-09 Update test 2 with new protocol
    added tests for battery and accelerometer also
2018-11-14 Cleaning up some of the tests, fixing missed protocol changes
2018-11-15 i always forget to call iteritems
2018-11-15 test to check if old badge timestamp is sent on sync
2018-11-15 Old tests for legacy protocol
2018-11-23 Adding link to programmer rig
2018-11-25 Implemented small Demo
2018-12-04 Revised Tinybuf generator and added documentation/README
2018-12-04 Renamed .md to .txt
2018-12-04 Updated README layout
2018-12-04 make sure we give badge time to restart before reconnecting
2018-12-05 Renamed README.txt to .md
2018-12-05 added manual badge speed test
2018-12-06 Added error indication by blinking red LED

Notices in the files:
parts and their libraries:
SparkFun-Electromechanical: Licensing: Creative Commons ShareAlike 4.0 International - https://creativecommons.org/licenses/by-sa/4.0
